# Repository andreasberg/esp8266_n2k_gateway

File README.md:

# NMEA2000 to WebSocket+Serial gateway 
Reads messages of N2K-bus and relaying over WebSocket and Serial 
### Functionality
- Listens for messages on NMEA 2000 (CANBus) bus and logs PGN of all messages received
- Writes same output over WebSocket and over Serial in Linux-'Tee'-like fashion (WebSocketBufferedStrem.h, inspired by [NeoTee](https://github.com/SlashDevin/NeoTee))
- Parses selected messages and logs
- Provides a simple yet (somewhat) responsive ([BootstrapV3](http://getbootstrap.com/)-based) web interface from the ESP8266 SPIFFS-filesystem
- Web-captive portal for configuration of WiFi-connecition
- Over-The-Air updates supported

### Dependencies
Depends on the following libraries (in addtion to the [`ESP8266 Core`](https://github.com/esp8266/Arduino) and [`Arduino IDE`](https://github.com/arduino/Arduino))
- [`arduinoWebSockets`](https://github.com/Links2004/arduinoWebSockets) - WebSocket Server and Client for Arduino
- [`CAN_BUS_Shield`](https://github.com/peppeve/CAN_BUS_Shield) - Can Bus Mcp2515 8/16 MHz oscillator 
- [`NMEA2000`](https://github.com/ttlappalainen/NMEA2000) - NMEA2000 library for Arduino 
- [`NMEA2000_mcp`](https://github.com/andreasberg/NMEA2000_mcp) - NMEA2000 library support for MCP2515 CAN bus controller. Forked version with added support for ESP8266 interrupts
- [`WiFiManager`](https://github.com/tzapu/WiFiManager) - ESP8266 WiFi Connection manager with web captive portal
- [`Arduino-Makefile-ESP`](https://github.com/andreasberg/Arduino-Makefile-ESP) - Arduino Makefile for ESP-boards 

### Building & flashing 

Edit the Makefile 
```make
  ARDMK_DIR := $(SRCDIR)/../Arduino-Makefile-ESP
  BOARD_TAG=huzzah
  ESP_OTA_ADDR=192.168.12.31
```
Then compile->link->hex
```sh
  make 
```
Normal upload (`esptool`) over USB-serial-FTDI 
```sh
  # first hit GPIO0+RST buttons on the Huzzah-board to enter flash-mode
  make upload 
  # sometimes the boot process hangs after upload, press RST to try again 
```
If the device for the USB-serial port in not detected correctly then override by defining MONITOR_PORT in Makefile
```make
  MONITOR_PORT=/dev/tty.usbserial-A104OFNV
```
A special target `monitor` in the makefile opens a screen-connection over serial
```sh
  make monitor
  # Ctrl-A k let's you terminate the serial connection
  # Connection needs to be terminated before 'make upload' or 'make upload_fs'
```
Once this (or any other sketch supporing Over-The-Air (OTA) updates) is successfully flashed, further uploads can be done with `espota.py` without putting board into flash-mode or closing serial connection(monitor)
Update Makefile:
```make
  ESP_OTA_ADDR=192.168.4.1
  ESP_OTA_PORT=8080           (default 8266)
  ESP_OTA_PWD=mysecret        (default <empty>)
```
and then
```sh
  make upload_ota
```
The webserver-files are located in [$(SRCDIR)/data](data) and the SPIFFS-file (filesystem binary image file) is created with makefile target `fs`
```sh
  make fs
```
and uploaded/flashed with
```sh
  make upload_fs
```
or
```sh
  make upload_fs_ota
```

After the board has booted and connected to Wifi, open a browser and go to `http://<IP>/index.html`

Default WebSocket-port is 81 so clicking 'Connect' shoud open the WebSocket-connection and start the feed of log-messages.

### Hardware

The ESP-module used is the [Adafruit HUZZAH ESP8266 breakout](https://learn.adafruit.com/adafruit-huzzah-esp8266-breakout/overview) with a "shield" providing
  - a CAN-bus interface (based on Microchip MCP2515- & MCP2562-ICs)
  - a switching regulator (based on Texas Instrument TPS54202-IC) for powering both the ESP8266-module and shield from the standard 12V supply of NMEA2000 bus

The schematic&board (EAGLE-)files can be found [here](hardware/esp8266_adafruit_huzzah_CAN_shield_with_Regulator)

Components of the shield are hand-solderable (minimum size 0705) but both the inductor (L1) and oscillator (Y1) are a bit tricky (should have a bit larger landing-pads)  

### ToDo/Limitations/Issues

- Implement more generic/lightwigth parse-to-log-function
  - The implementation for parsing the N2k messages is a simple rip of NMEA2000-library DataDisplay-examples and quite heavy. Only a few messages can be handled before exhausting the ESP8266's very limited .text-section (max 32 KB, linker error: section '.text' will not fit in region 'iram1_0_seg'). I assume the WiFiManager & arduinoWebSockets are also to blame for bloating the section. 
- Design shield version 2 for more cost effective ESP8266-modules like the Wemos D1 Mini

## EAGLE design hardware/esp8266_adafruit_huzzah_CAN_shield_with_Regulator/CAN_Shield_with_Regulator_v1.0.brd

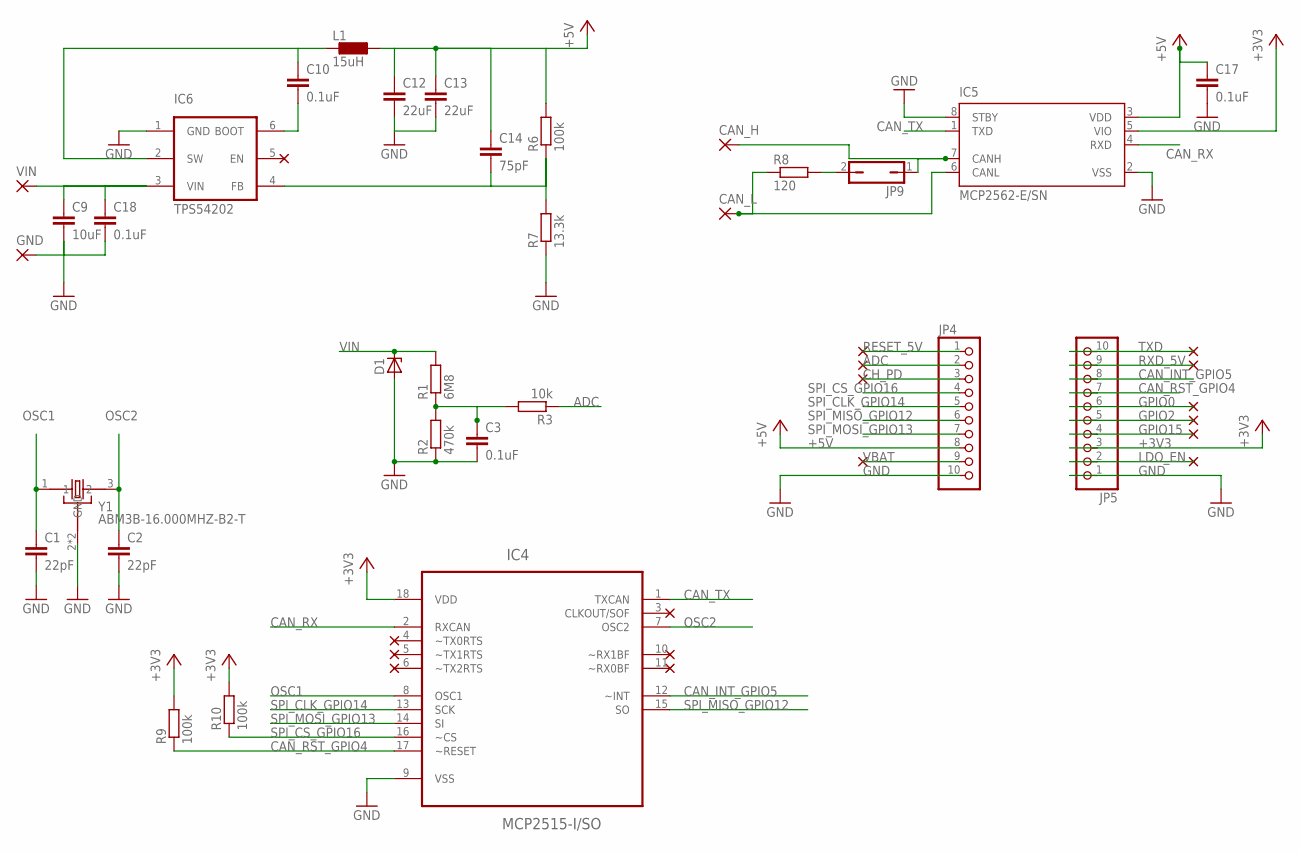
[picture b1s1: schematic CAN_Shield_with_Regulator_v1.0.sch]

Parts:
C1, C2: 22pF; C0805
C3, C10, C17, C18: 0.1uF; C1206
C9: 10uF; C1206
C12, C13: 22uF; C1206
C14: 75pF; C1206
CAN_H: WIREPADSMD5-2,5; 5-2,5
CAN_L: WIREPADSMD5-2,5; 5-2,5
D1: ZENER-DIODE; SOD3715X135N
GND: WIREPADSMD5-2,5; 5-2,5
IC4: MCP2515-I/SO; SOIC127P1034X264-18N
IC5: MCP2562-E/SN; SOIC127P600X175-8N
IC6: TPS54202; SOT3-6P
JP4, JP5: HEADER-1X1070MIL; 1X10_ROUND70
JP9: JP1Q; JP1
L1: 15uH; ER1515AH
R1: 6M8; R1206
R2: 470k; R1206
R3: 10k; R1206
R6, R9, R10: 100k; R1206
R7: 13.3k; R1206
R8: 120; R1206
VIN: WIREPADSMD5-2,5; 5-2,5
Y1: ABM3B-16.000MHZ-B2-T; OSCSC500X320X110-4N

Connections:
+3V3: IC4.18 (VDD), IC5.5 (VIO), JP5.3, R9.2, R10.2
+5V: C12.1, C13.1, C14.1, C17.1, IC5.3 (VDD), JP4.8, L1.P$1 (1), R6.2
ADC: JP4.2, R3.1
CAN_H: CAN_H.1, IC5.7 (CANH), JP9.1
CAN_INT_GPIO5: IC4.12 (~INT), JP5.8
CAN_L: CAN_L.1, IC5.6 (CANL), R8.1
CAN_RST_GPIO4: IC4.17 (~RESET), JP5.7, R9.1
CAN_RX: IC4.2 (RXCAN), IC5.4 (RXD)
CAN_TX: IC4.1 (TXCAN), IC5.1 (TXD)
CH_PD: JP4.3
GND: C1.2, C2.2, C3.2, C9.2, C12.2, C13.2, C17.2, C18.2, D1.A, GND.1, IC4.9 (VSS), IC5.2 (VSS), IC5.8 (STBY), IC6.1 (GND), JP4.10, JP5.1, R2.1, R7.1, Y1.2 (GND), Y1.4 (GND)
GPIO0: JP5.6
GPIO2: JP5.5
GPIO15: JP5.4
LDO_EN: JP5.2
unnamed: C3.1, R1.1, R2.2, R3.2
unnamed: C10.2, IC6.6 (BOOT)
unnamed: C10.1, IC6.2 (SW), L1.P$2 (2)
unnamed: C14.2, IC6.4 (FB), R6.1, R7.2
unnamed: JP9.2, R8.2
OSC1: C1.1, IC4.8 (OSC1), Y1.1
OSC2: C2.1, IC4.7 (OSC2), Y1.3 (2)
RESET_5V: JP4.1
RXD_5V: JP5.9
SPI_CLK_GPIO14: IC4.13 (SCK), JP4.5
SPI_CS_GPIO16: IC4.16 (~CS), JP4.4, R10.1
SPI_MISO_GPIO12: IC4.15 (SO), JP4.6
SPI_MOSI_GPIO13: IC4.14 (SI), JP4.7
TXD: JP5.10
VBAT: JP4.9
VIN: C9.1, C18.1, D1.C, IC6.3 (VIN), R1.2, VIN.1

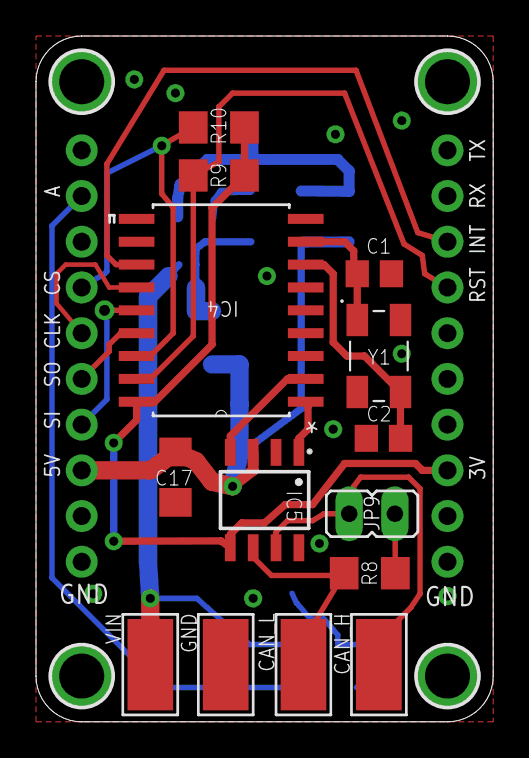
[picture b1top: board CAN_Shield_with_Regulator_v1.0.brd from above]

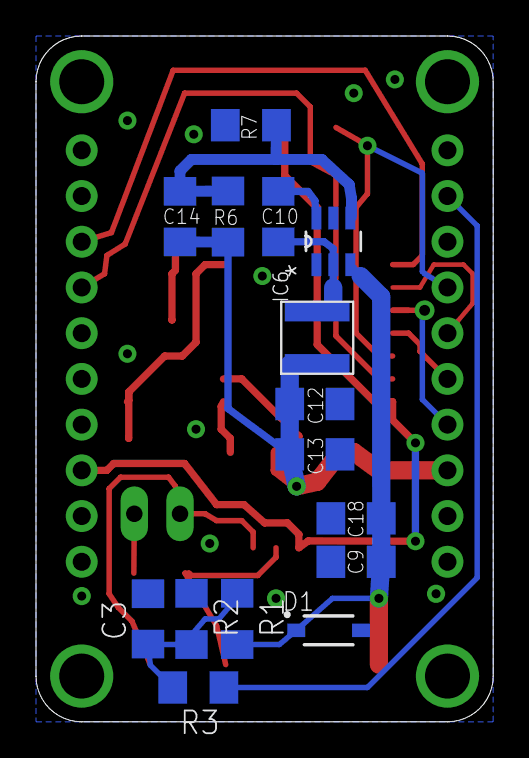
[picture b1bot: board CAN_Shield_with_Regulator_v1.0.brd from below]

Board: 2 copper layers, 25.4 x 38.1 mm, 36 parts (16 on the bottom side), 22 nets.

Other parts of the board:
E$1, E$2, E$3, E$4: MOUNTINGHOLE_2.5_PLATED
U$23: HUZZAHLOGO

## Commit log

2017-06-02 Add support for OTA updates
2017-06-08 Simpler implementation of WebSocket+Stream “Tee”-function by buffering single character writes before flushing to WebSocket
2017-06-08 Changed WebSocket “Tee”-function
2017-06-09 Changed Makefile-framework from makeEspArduino to Arduino-Makefile-ESP
2017-06-09 Removed tools
2017-06-09 Added EAGLE-files for the CANBus Shield used by the esp8266_n2k_gateway
2017-06-09 Added pdfs of board and schematic
2017-06-09 Added screen shot
2017-06-09 Cleanup

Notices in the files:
parts and their libraries:
microbuilder: This work is placed in the public domain, and may be freely used for commercial and non-commercial work with the following conditions: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
